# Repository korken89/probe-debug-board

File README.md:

# Probe debug board for cheap logic analyzers

A simple board to probe the SWD/JTAG signals from a debug probe.

Designed to work with a cheap "24 MHz usb logic analyzer", can be found on Aliexpress or similar.

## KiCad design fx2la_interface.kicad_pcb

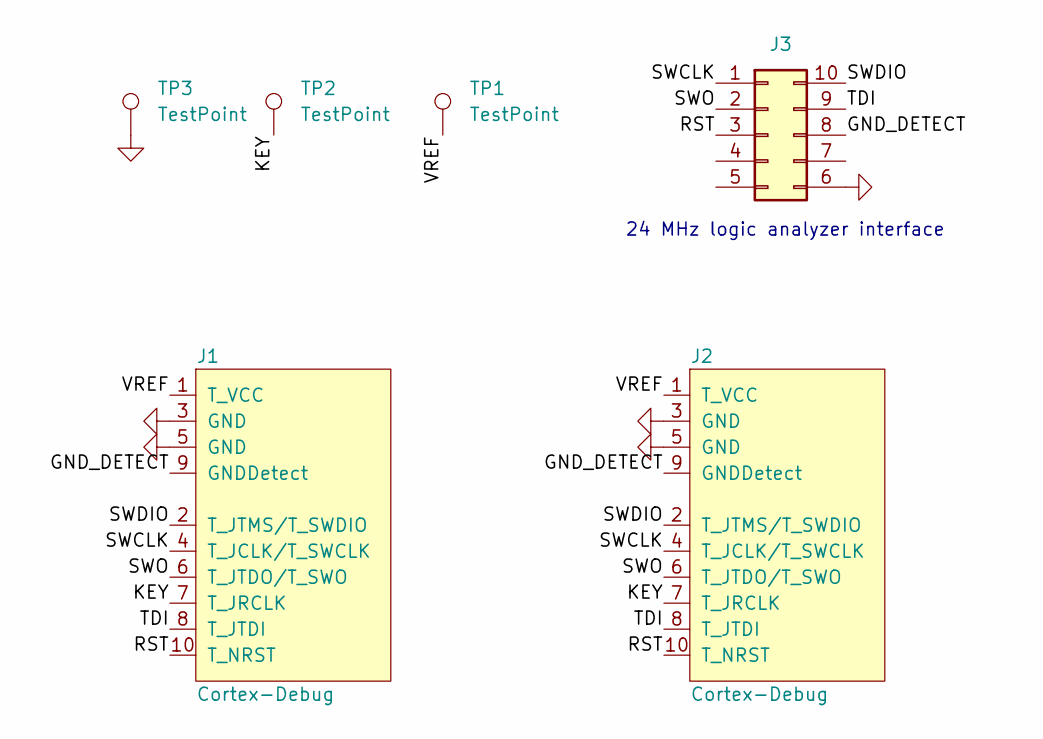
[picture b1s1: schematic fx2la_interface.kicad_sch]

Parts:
J1, J2: Cortex-Debug; PinHeader_2x05_FTSH-105-01-L-DV-K
J3: Conn_02x05_Counter_Clockwise; 2x5_2.54mm_side
TP1, TP2, TP3: TestPoint; pad_1.5x2.0mm

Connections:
/GND_DETECT: J1.9 (GNDDetect), J2.9 (GNDDetect), J3.8
/KEY: J1.7 (T_JRCLK), J2.7 (T_JRCLK), TP2.1
/RST: J1.10 (T_NRST), J2.10 (T_NRST), J3.3
/SWCLK: J1.4 (T_JCLK/T_SWCLK), J2.4 (T_JCLK/T_SWCLK), J3.1
/SWDIO: J1.2 (T_JTMS/T_SWDIO), J2.2 (T_JTMS/T_SWDIO), J3.10
/SWO: J1.6 (T_JTDO/T_SWO), J2.6 (T_JTDO/T_SWO), J3.2
/TDI: J1.8 (T_JTDI), J2.8 (T_JTDI), J3.9
/VREF: J1.1 (T_VCC), J2.1 (T_VCC), TP1.1
GND: J1.3 (GND), J1.5 (GND), J2.3 (GND), J2.5 (GND), J3.6, TP3.1

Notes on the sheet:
24 MHz logic analyzer interface

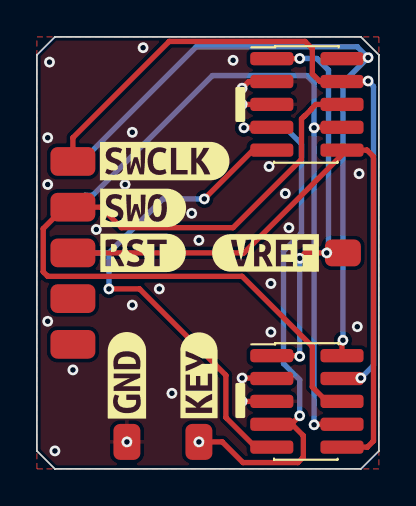
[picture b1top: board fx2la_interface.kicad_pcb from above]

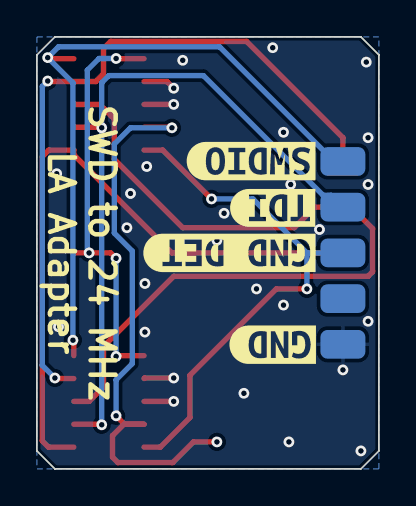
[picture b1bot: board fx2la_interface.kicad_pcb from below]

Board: 2 copper layers, 19.0 x 24.0 mm, 16 parts (4 on the bottom side), 9 nets.

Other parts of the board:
kibuzzard-63A316D6: G***; kibuzzard-63A316D6
kibuzzard-639836A5: G***; kibuzzard-639836A5
kibuzzard-639836BA: G***; kibuzzard-639836BA
kibuzzard-639836D5: G***; kibuzzard-639836D5
kibuzzard-639836EB: G***; kibuzzard-639836EB
kibuzzard-639836FB: G***; kibuzzard-639836FB
kibuzzard-6398368A: G***; kibuzzard-6398368A
kibuzzard-6398369A: G***; kibuzzard-6398369A
kibuzzard-6398370D: G***; kibuzzard-6398370D
kibuzzard-63983677: G***; kibuzzard-63983677

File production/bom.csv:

Designator,Footprint,Quantity,Value,LCSC Part #
"J1, J2",PinHeader_2x05_FTSH-105-01-L-DV-K,2,Cortex-Debug,
J3,2x5_2.54mm_side,1,Conn_02x05_Counter_Clockwise,

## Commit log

2022-12-21 Save
2022-12-21 Separate connectors more
